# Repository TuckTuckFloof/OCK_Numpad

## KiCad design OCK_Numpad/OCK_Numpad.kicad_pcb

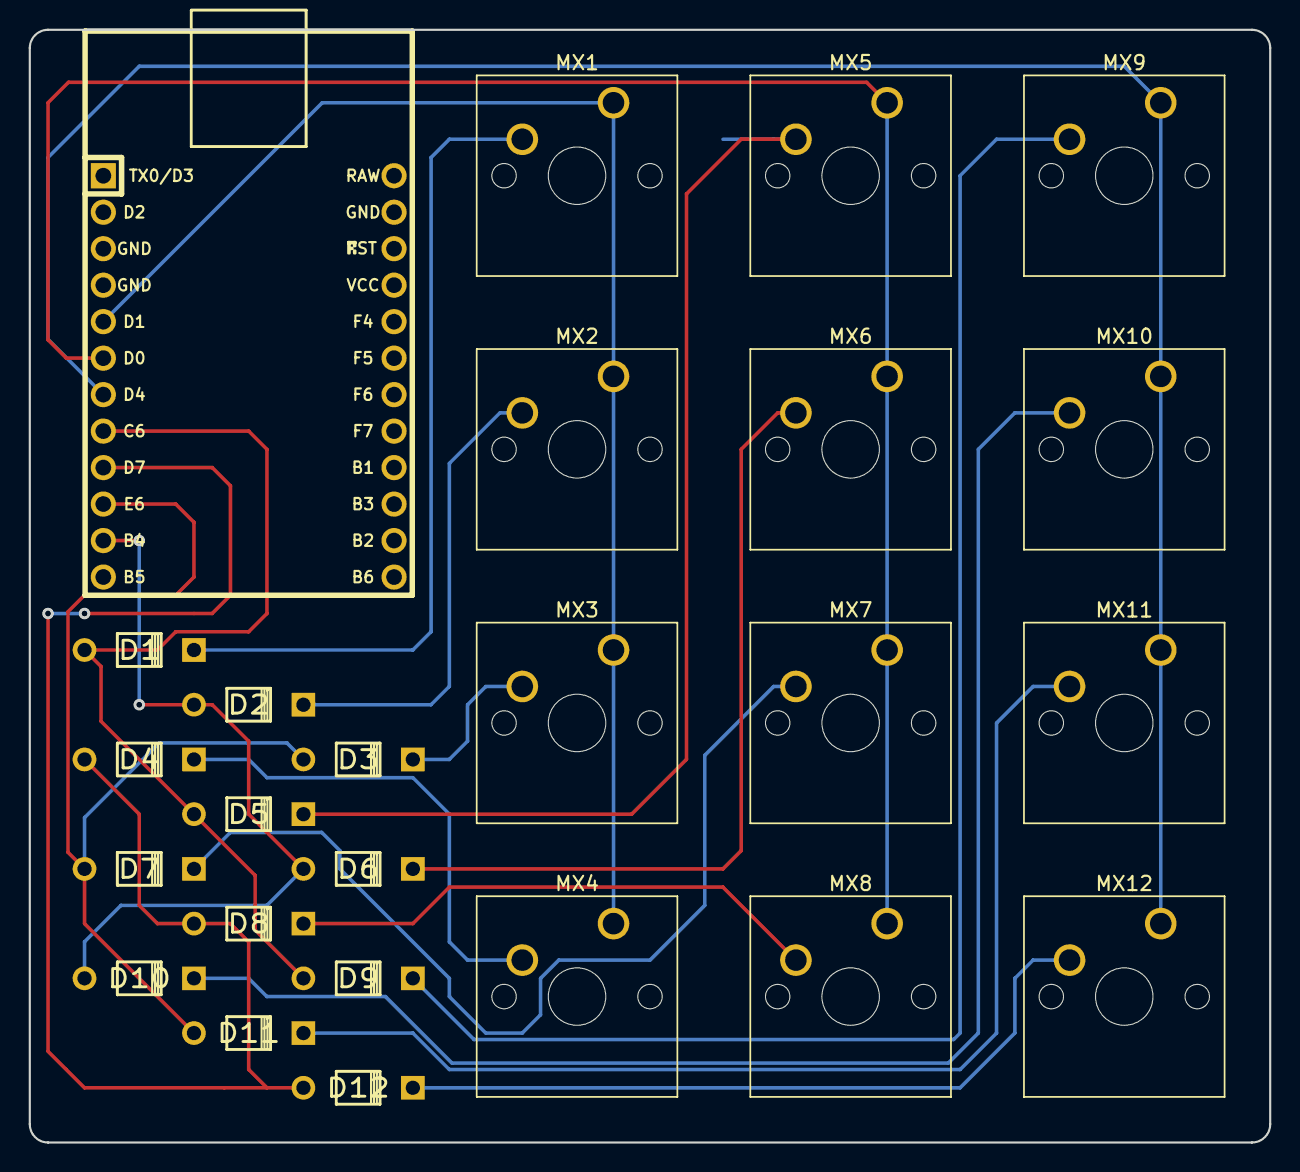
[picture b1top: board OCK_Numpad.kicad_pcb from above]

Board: 2 copper layers, 86.4 x 77.5 mm, 25 parts (0 on the bottom side), 19 nets.

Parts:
D1, D2, D3, D4, D5, D6, D7, D8, D9, D10, D11, D12: D_Small; Diode
MX1, MX2, MX3, MX4, MX5, MX6, MX7, MX8, MX9, MX10, MX11, MX12: MX-NoLED; SW_Cherry_MX_1.00u_PCB
U1: ProMicro; ArduinoProMicro-Mini-USB

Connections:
Col0: MX1.1, MX2.1, MX3.1, MX4.1, U1.5
Col1: MX5.1, MX6.1, MX7.1, MX8.1, U1.6
Col2: MX9.1, MX10.1, MX11.1, MX12.1, U1.7
unnamed: D1.2, MX1.2
unnamed: D2.2, MX2.2
unnamed: D3.2, MX3.2
unnamed: D4.2, MX4.2
unnamed: D5.2, MX5.2
unnamed: D6.2, MX6.2
unnamed: D7.2, MX7.2
unnamed: D8.2, MX8.2
unnamed: D9.2, MX9.2
unnamed: D10.2, MX10.2
unnamed: D11.2, MX11.2
unnamed: D12.2, MX12.2
Row0: D1.1, D5.1, D9.1, U1.8
Row1: D2.1, D6.1, D10.1, U1.11
Row2: D3.1, D7.1, D11.1, U1.10
Row3: D4.1, D8.1, D12.1, U1.9

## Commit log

2020-08-26 Got it all wired up and ready to add the extra layouts + silks
2020-08-27 Added folder for extra files and gerbers + a step file
2020-10-21 Updating because Distro hopping lol
